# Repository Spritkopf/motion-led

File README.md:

## motion-led

Source code for the motion controlled led night light

### code

Firmware. This is a generic Makefile project. Building was tested using the GNU Arm Embedded toolchain.
Build with:

```bash
make BINPATH=<path/to/gnu/arm/embedded/toolchain/bin>     #(without trailing slash / !)
```

the BINPATH=... argument is not necessary if you have the binaries in your PATH

Also there are eclipse project files for use in eclipse with the Gnu Mcu Eclipse plugin. Use the "Import Existing Code" feature in eclipse

### pcb

PCB design data as well as gerber files

### cad

Contains everything related to the housing

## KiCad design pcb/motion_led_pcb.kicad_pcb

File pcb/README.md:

### PCB Design data

PCB design was created in KiCad

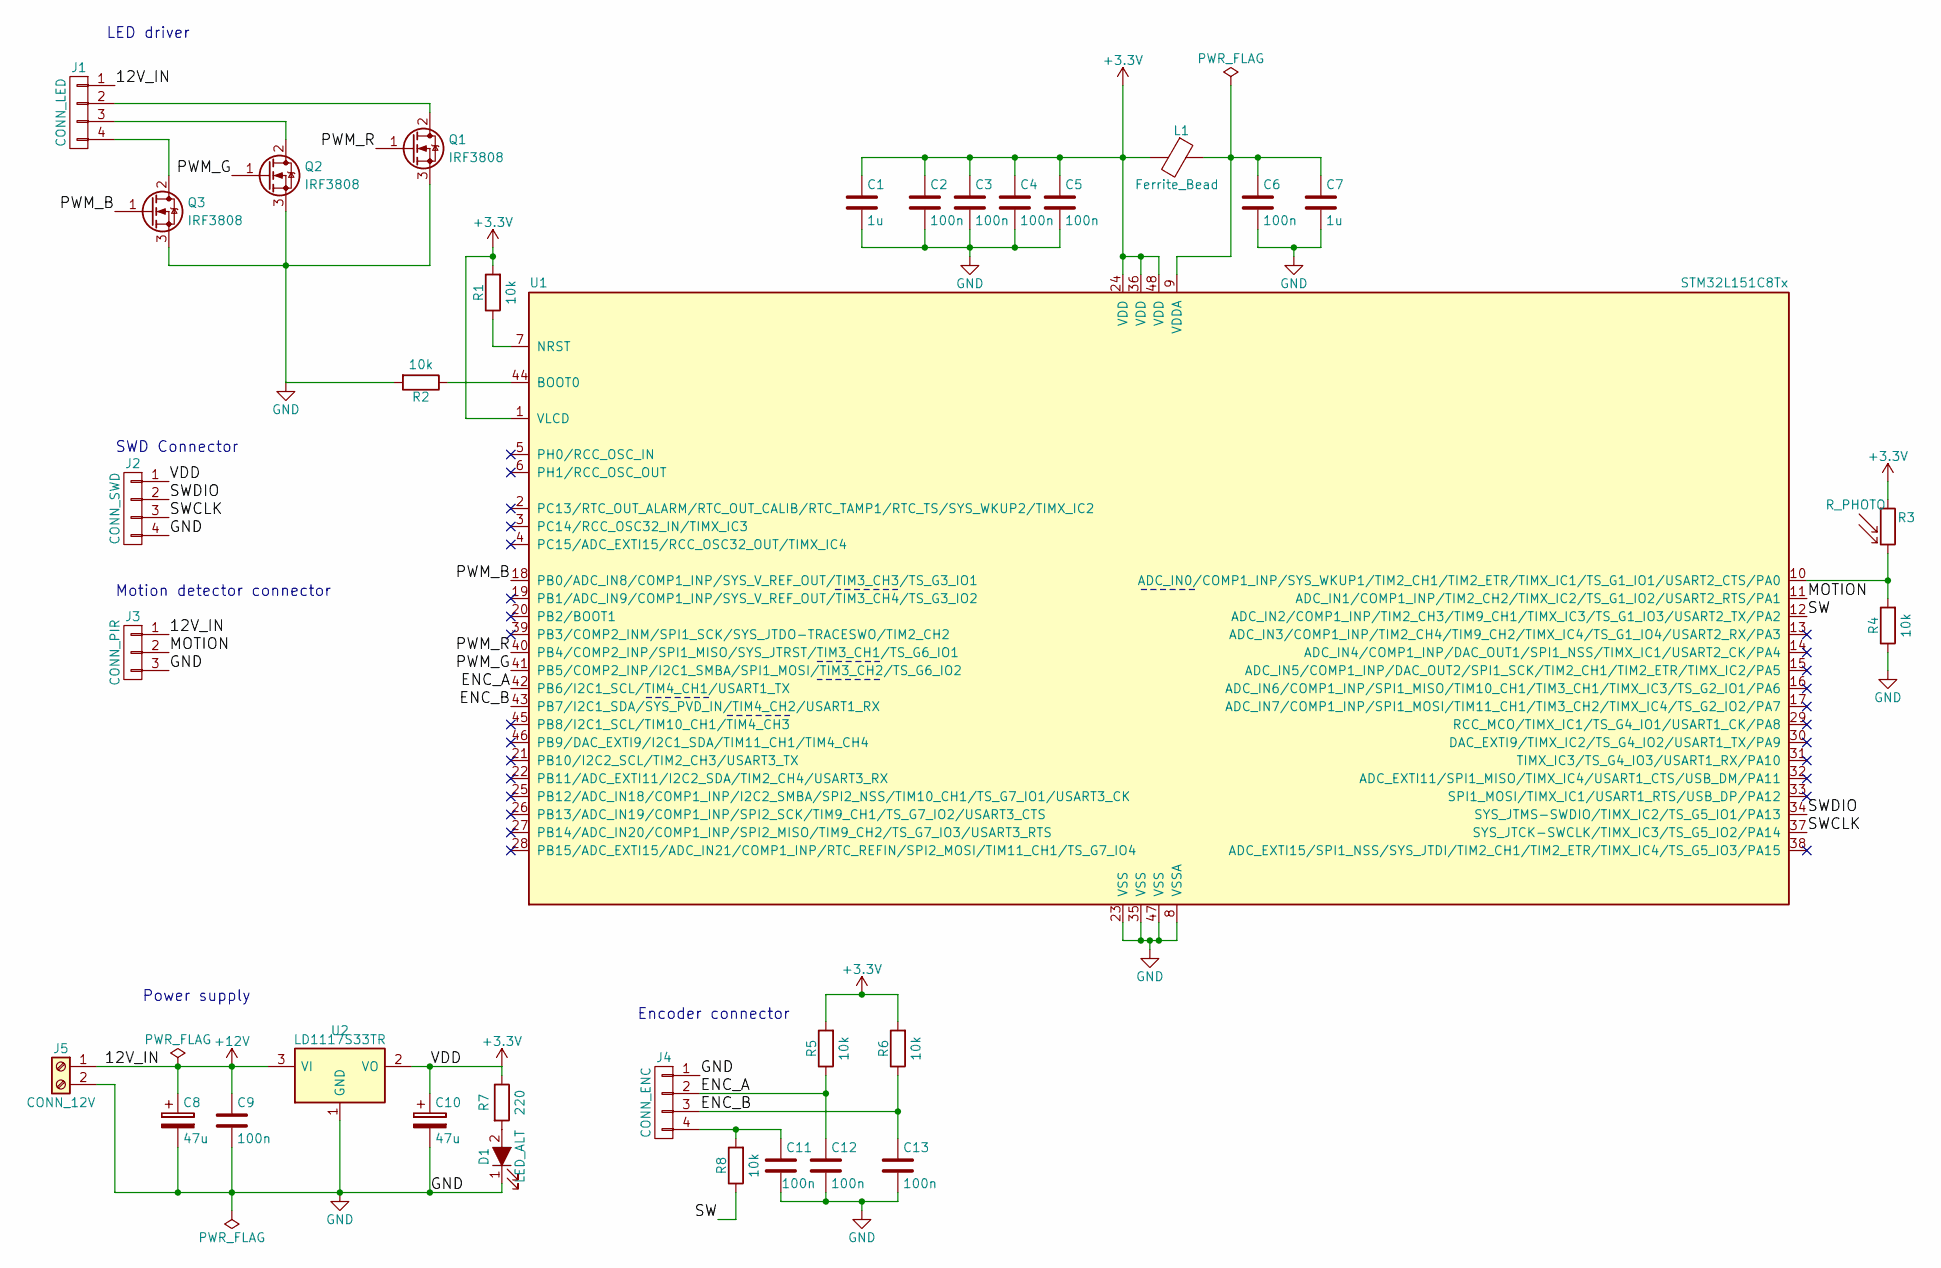
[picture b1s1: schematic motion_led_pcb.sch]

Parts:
C1, C7: 1u; C_1206_HandSoldering
C2, C3, C4, C5, C6, C9, C11, C12, C13: 100n; C_1206_HandSoldering
C8, C10: 47u; CP_Elec_10x10
D1: LED_ALT; LED_1206_HandSoldering
J1: CONN_LED; Pin_Header_Angled_1x04_Pitch2.54mm
J2: CONN_SWD; Pin_Header_Straight_1x04_Pitch2.54mm
J3: CONN_PIR; Pin_Header_Angled_1x04_Pitch2.54mm
J4: CONN_ENC; Pin_Header_Straight_1x04_Pitch2.54mm
J5: CONN_12V; TerminalBlock_WAGO-804_RM5mm_2pol
L1: Ferrite_Bead; L_0805_HandSoldering
Q1, Q2, Q3: IRF3808; TO-220_Vertical
R1, R2, R4, R5, R6, R8: 10k; R_1206_HandSoldering
R3: R_PHOTO; Pin_Header_Straight_1x02_Pitch2.54mm
R7: 220; R_1206_HandSoldering
U1: STM32L151C8Tx; LQFP-48_7x7mm_Pitch0.5mm
U2: LD1117S33TR; SOT-223

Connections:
+3V3: C1.1, C2.1, C3.1, C4.1, C5.1, C10.1, J2.1, L1.2, R1.2, R3.1, R5.2, R6.2, R7.1, U1.1 (VLCD), U1.24 (VDD), U1.36 (VDD), U1.48 (VDD), U2.2 (VO)
+12V: C8.1, C9.1, J1.1, J3.1, J5.1, U2.3 (VI)
/ENC_A: C12.1, J4.2, R5.1, U1.42 (PB6/I2C1_SCL/TIM4_CH1/USART1_TX)
/ENC_B: C13.1, J4.3, R6.1, U1.43 (PB7/I2C1_SDA/SYS_PVD_IN/TIM4_CH2/USART1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)
/MOTION: J3.2, U1.11 (ADC_IN1/COMP1_INP/TIM2_CH2/TIMX_IC2/TS_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)
/PWM_B: Q3.1 (G), U1.18 (PB0/ADC_IN8/COMP1_INP/SYS_V_REF_OUT/TIM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)
/PWM_G: Q2.1 (G), U1.41 (PB5/COMP2_INP/I2C1_SMBA/SPI1_MOSI/TIM3_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)
/PWM_R: Q1.1 (G), U1.40 (PB4/COMP2_INP/SPI1_MISO/SYS_JTRST/TIM3_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)
/SW: R8.1, U1.12 (ADC_IN2/COMP1_INP/TIM2_CH3/TIM9_CH1/TIM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)
/SWCLK: J2.3, U1.37 (SYS_JTCK-SWCLK/TIMX_IC3/TS_G5_IO2/PA14)
/SWDIO: J2.2, U1.34 (SYS_JTMS-SWDIO/TIMX_IC2/TS_G5_IO1/PA13)
GND: C1.2, C2.2, C3.2, C4.2, C5.2, C6.2, C7.2, C8.2, C9.2, C10.2, C11.2, C12.2, C13.2, D1.1 (K), J2.4, J3.3, J4.1, J5.2, Q1.3 (S), Q2.3 (S), Q3.3 (S), R2.2, R4.1, U1.8 (VSSA), U1.23 (VSS), U1.35 (VSS), U1.47 (VSS), U2.1 (GND); also elsewhere on the board
unnamed: C6.1, C7.1, L1.1, U1.9 (VDDA)
unnamed: C11.1, J4.4, R8.2
unnamed 14: D1.2 (A), R7.2; also elsewhere on the board
unnamed: J1.2, Q1.2 (D)
unnamed: J1.3, Q2.2 (D)
unnamed: J1.4, Q3.2 (D)
unnamed: R1.1, U1.7 (NRST)
unnamed: R2.1, U1.44 (BOOT0)
unnamed: R3.2, R4.2, U1.10 (ADC_IN0/COMP1_INP/SYS_WKUP1/TIM2_CH1/TI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)

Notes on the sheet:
Encoder connector
Power supply
LED driver
Motion detector connector
SWD Connector

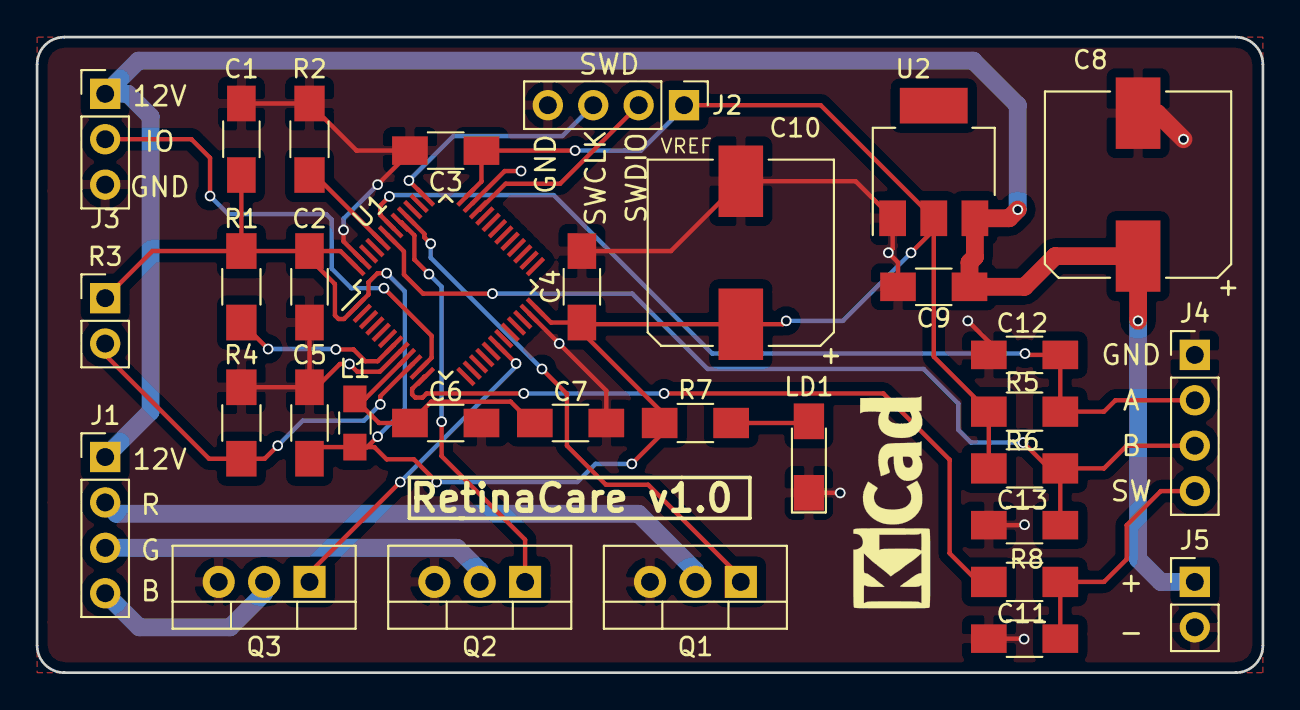
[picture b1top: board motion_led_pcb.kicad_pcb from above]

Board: 2 copper layers, 68.6 x 35.6 mm, 33 parts (0 on the bottom side), 21 nets.

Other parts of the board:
LD1: LED_ALT; LED_1206_HandSoldering

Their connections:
GND: LD1.1; also elsewhere on the board
unnamed 14: LD1.2; also elsewhere on the board

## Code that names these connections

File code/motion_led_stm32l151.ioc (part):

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Mcu.Name=STM32L151C(6-8-B)Tx
Mcu.Package=LQFP48
Mcu.UserName=STM32L151C8Tx
PA0-WKUP1.GPIOParameters=GPIO_Label
PA0-WKUP1.GPIO_Label=PHOTO_R
PA0-WKUP1.Mode=IN0
PA0-WKUP1.Signal=ADC_IN0
PA1.GPIOParameters=GPIO_Label
PA1.GPIO_Label=MOTION
PA1.Signal=GPXTI1
PA13.Mode=Serial_Wire
PA13.Signal=SYS_JTMS-SWDIO
PA14.Mode=Serial_Wire
PA14.Signal=SYS_JTCK-SWCLK
PA2.GPIOParameters=GPIO_Label
PA2.GPIO_Label=ENC_BTN
PA2.Signal=GPXTI2
PB0.GPIOParameters=GPIO_Label
PB0.GPIO_Label=PWM_Blue
PB0.Signal=S_TIM3_CH3
PB4.GPIOParameters=GPIO_Label
PB4.GPIO_Label=PWM_Red
PB4.Signal=S_TIM3_CH1
PB5.GPIOParameters=GPIO_Label
PB5.GPIO_Label=PWM_Green
PB5.Signal=S_TIM3_CH2
PB6.GPIOParameters=GPIO_Label
PB6.GPIO_Label=ENC_A
PB6.Signal=S_TIM4_CH1
PB7.GPIOParameters=GPIO_Label
PB7.GPIO_Label=ENC_B
PB7.Signal=S_TIM4_CH2
RCC.HSE_VALUE=24000000
RCC.SYSCLKFreq_VALUE=12000000
RCC.SYSCLKSource=RCC_SYSCLKSOURCE_PLLCLK

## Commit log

2017-08-23 first commit: basic project for GnuArmEclipse (based on CMSIS Packs plugin)
2017-08-23 added pwm and colorwheel modules, pwm verified working
2017-11-09 first version of fw for final board based on STM32L1
    - working hardware layer for LED-strip pwm
    - working hardware layer for rotary encoder
    - test programm: blink red / blue when rotating the encoder
    - cleanup of repository: remove stm32f4discovery test project
    - add LICENSE
2017-11-11 add encoder button functionality
2017-11-11 - add .gitignore (do not upload build directory / binaries) - add motion sensor module - some generalization regarding interrupt handling (introducing callback hell)
2017-11-13 - add settings module: save rgb data in persistent eeprom memory
2017-11-24 - introduced statemachine + refactoring
    - main program logic handled by state machine (not yet finished)
    - added motino sensor
    - working: fading in and out when a motion is detected
    - refactoring: added a abstraction layer for the rgb_led so the
    pwm/colorwheel handling gets less confusing
    - changed structure of persistent memory, now hold only color angle and
2017-11-27 Add color selection
    - pushing button enters color selection mode. The leds will show current
    hue and brightness. Rotating the encoder will change hue. Select desired
    color with button press. LEDs will blink shortly to confirm selection.
    - after selecting hue, brightness selection mode is entered. Rotating
    the encoder will change brightness. Select desired brightness with
    button press. LEDs will blink twice shortly to confirm selection. The
2017-11-29 add light sensor
    - add adc module for reading photoresistor voltage
    - add module "light_sensor" as wrapper for adc
    - while waking up, the firmware checks the ADC threshold and continues
    only if it is dark outside
    - threshold can be changed in file light_sensor.c
    - todo: add low power modes
2017-12-06 begin model of housing
2017-12-07 further work on housing
2018-01-05 Revert "further work on housing"
    This reverts commit a4d4fc7b077d78782a1bc928010f73d2f7b85a85.
2018-01-05 project cleanup
    changed makefile and eclipse project settings for better platform
    independence.
    - The eclipse project should now work out of the box if the
    GNU MCU Eclipse plugin is configurted properly (toolchain paths !)
    - using 'make' is now possible without the BINPATH parameter, if the
    toolchain binaries are in PATH
2018-01-05 Revert "Revert "further work on housing""
    This reverts commit 258873a0c46fc528692b93963fde2261351ec5b1.
2018-01-09 introduced low power mode
    - device enters "STOP" mode
    - wakeup when interupts occur (motion sensor or rotary encoder)
    - needs testing / confirmation
2018-01-09 - first version finished
    - sleep mode tested
    - added missing CAD parts
    - set time the lights will stay on to 2 minutes
2018-01-11 try out STOP mode which needs even less power than sleep mode.
2018-01-11 changed fade in/out
    - seperated fade-out time from fade-in time
    - make fade out longer to make it easier to react if it was too soon
2018-01-11 improved behavior when turning off
    The time the light stays on is no longer fixed. If a movement is
    recognized at the end of the on-time, the light will stay on for 10
    additional seconds (The motion sensor has to be configured in
    "repeatable trigger" mod so that the output stays high as long there is
    movement)
    If a movement occurs during fade-out, the light will turn back on for
2018-01-11 - fixed encoder rotation
    - clockwise to increase brightness feels more natural
2018-01-13 new feature: turn off if external light is detected after wakeup
    - light sensor value is saved when chosing color/brightness
    - if light sensor reads more than this value at/after fade-in, it is
    assumed that an external light is switched on and sleep mode is entered
2018-01-22 increased treshold for external light detection
